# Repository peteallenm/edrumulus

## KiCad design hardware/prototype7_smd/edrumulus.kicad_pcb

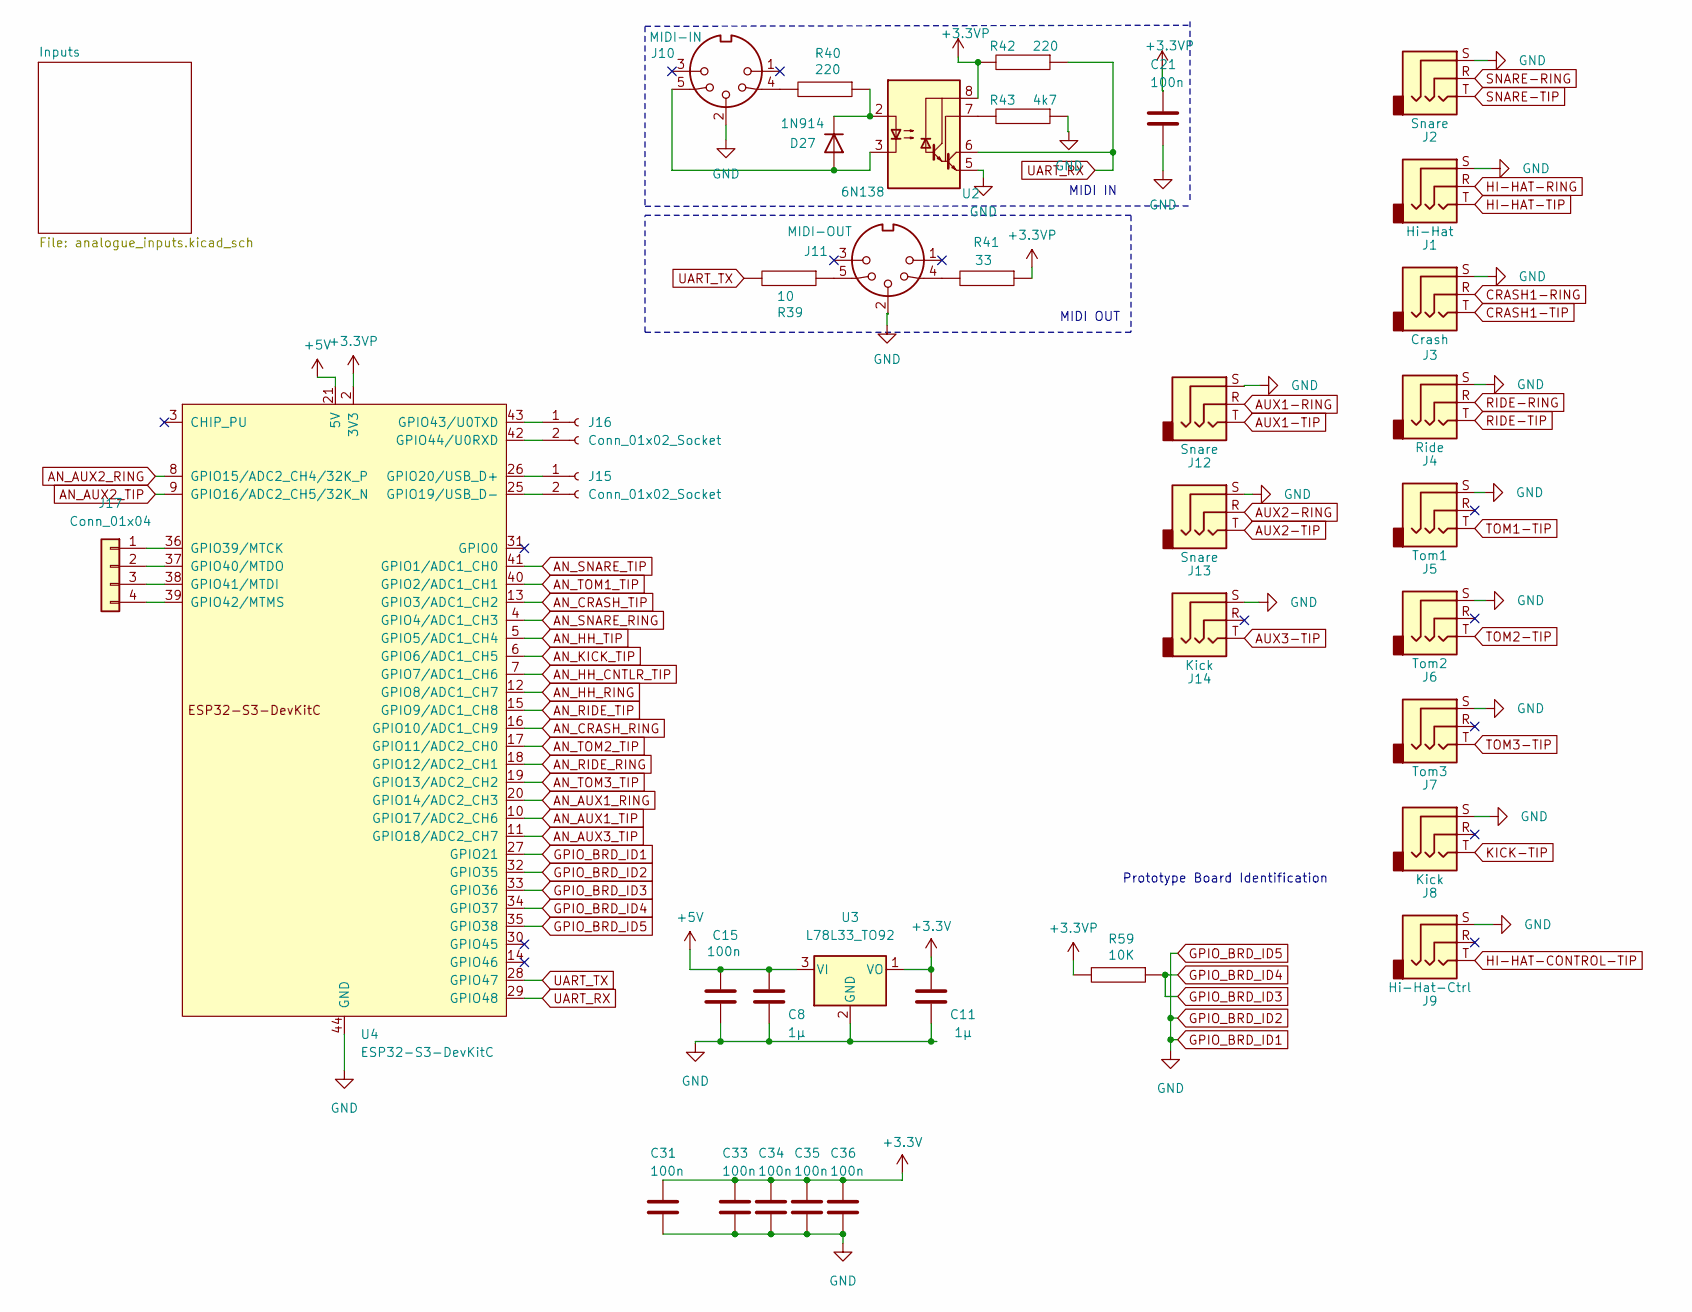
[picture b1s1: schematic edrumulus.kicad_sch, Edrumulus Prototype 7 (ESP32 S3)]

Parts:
C8, C11: 1µ; C_1206_3216Metric
C15, C21, C31, C33, C34, C35, C36: 100n; C_1206_3216Metric
D27: 1N914; D_DO-35_SOD27_P7.62mm_Horizontal
J1: Hi-Hat; Jack_6.35mm_Neutrik_NMJ6HCD2_Horizontal
J2, J12, J13: Snare; Jack_6.35mm_Neutrik_NMJ6HCD2_Horizontal
J3: Crash; Jack_6.35mm_Neutrik_NMJ6HCD2_Horizontal
J4: Ride; Jack_6.35mm_Neutrik_NMJ6HCD2_Horizontal
J5: Tom1; Jack_6.35mm_Neutrik_NMJ6HCD2_Horizontal
J6: Tom2; Jack_6.35mm_Neutrik_NMJ6HCD2_Horizontal
J7: Tom3; Jack_6.35mm_Neutrik_NMJ6HCD2_Horizontal
J8, J14: Kick; Jack_6.35mm_Neutrik_NMJ6HCD2_Horizontal
J9: Hi-Hat-Ctrl; Jack_6.35mm_Neutrik_NMJ6HCD2_Horizontal
J10: MIDI-IN; DIN-5
J11: MIDI-OUT; DIN-5
J15, J16: Conn_01x02_Socket; PinHeader_1x02_P2.54mm_Vertical
J17: Conn_01x04; PinHeader_1x04_P2.54mm_Vertical
R39: 10; R_1206_3216Metric
R40, R42: 220; R_1206_3216Metric
R41: 33; R_1206_3216Metric
R43: 4k7; R_1206_3216Metric
R59: 10K; R_1206_3216Metric
U2: 6N138; DIP-8_W7.62mm_Socket
U3: L78L33_TO92; TO-92_Inline
U4: ESP32-S3-DevKitC

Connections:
+3.3V: C11.1, C31.1, C33.1, C34.1, C35.1, C36.1, U3.1 (VO); also elsewhere on the board
+3.3VP: C21.1, R41.1, R42.2, R59.2, U2.8 (VCC), U4.1 (3V3), U4.2 (3V3)
+5V: C8.1, C15.1, U3.3 (VI), U4.21 (5V)
AN_AUX1_RING: U4.20 (GPIO14/ADC2_CH3); also elsewhere on the board
AN_AUX1_TIP: U4.10 (GPIO17/ADC2_CH6); also elsewhere on the board
AN_AUX2_RING: U4.8 (GPIO15/ADC2_CH4/32K_P); also elsewhere on the board
AN_AUX2_TIP: U4.9 (GPIO16/ADC2_CH5/32K_N); also elsewhere on the board
AN_AUX3_TIP: U4.11 (GPIO18/ADC2_CH7); also elsewhere on the board
AN_CRASH_RING: U4.16 (GPIO10/ADC1_CH9); also elsewhere on the board
AN_CRASH_TIP: U4.13 (GPIO3/ADC1_CH2); also elsewhere on the board
AN_HH_CNTLR_TIP: U4.7 (GPIO7/ADC1_CH6); also elsewhere on the board
AN_HH_RING: U4.12 (GPIO8/ADC1_CH7); also elsewhere on the board
AN_HH_TIP: U4.5 (GPIO5/ADC1_CH4); also elsewhere on the board
AN_KICK_TIP: U4.6 (GPIO6/ADC1_CH5); also elsewhere on the board
AN_RIDE_RING: U4.18 (GPIO12/ADC2_CH1); also elsewhere on the board
AN_RIDE_TIP: U4.15 (GPIO9/ADC1_CH8); also elsewhere on the board
AN_SNARE_RING: U4.4 (GPIO4/ADC1_CH3); also elsewhere on the board
AN_SNARE_TIP: U4.41 (GPIO1/ADC1_CH0); also elsewhere on the board
AN_TOM1_TIP: U4.40 (GPIO2/ADC1_CH1); also elsewhere on the board
AN_TOM2_TIP: U4.17 (GPIO11/ADC2_CH0); also elsewhere on the board
AN_TOM3_TIP: U4.19 (GPIO13/ADC2_CH2); also elsewhere on the board
AUX1-RING: J12.R; also elsewhere on the board
AUX1-TIP: J12.T; also elsewhere on the board
AUX2-RING: J13.R; also elsewhere on the board
AUX2-TIP: J13.T; also elsewhere on the board
AUX3-TIP: J14.T; also elsewhere on the board
CRASH1-RING: J3.R; also elsewhere on the board
CRASH1-TIP: J3.T; also elsewhere on the board
GPIO_BRD_ID1: C8.2, C11.2, C15.2, C21.2, C31.2, C33.2, C34.2, C35.2, C36.2, J1.S, J2.S, J3.S, J4.S, J5.S, J6.S, J7.S, J8.S, J9.S, J10.2, J11.2, J12.S, J13.S, J14.S, R43.1, U2.5 (GND), U3.2 (GND), U4.22 (GND), U4.23 (GND), U4.24 (GND), U4.27 (GPIO21), U4.32 (GPIO35), U4.35 (GPIO38), U4.44 (GND); also elsewhere on the board
GPIO_BRD_ID3: R59.1, U4.33 (GPIO36), U4.34 (GPIO37)
HI-HAT-CONTROL-TIP: J9.T; also elsewhere on the board
HI-HAT-RING: J1.R; also elsewhere on the board
HI-HAT-TIP: J1.T; also elsewhere on the board
KICK-TIP: J8.T; also elsewhere on the board
unnamed: D27.2 (A), J10.5, U2.3 (C2)
unnamed: D27.1 (K), R40.1, U2.2 (C1)
unnamed: J10.4, R40.2
unnamed: J11.4, R41.2
unnamed: J11.5, R39.1
unnamed: J15.1, U4.26 (GPIO20/USB_D+)
unnamed: J15.2, U4.25 (GPIO19/USB_D-)
unnamed: J16.1, U4.43 (GPIO43/U0TXD)
unnamed: J16.2, U4.42 (GPIO44/U0RXD)
unnamed: J17.1, U4.36 (GPIO39/MTCK)
unnamed: J17.2, U4.37 (GPIO40/MTDO)
unnamed: J17.3, U4.38 (GPIO41/MTDI)
unnamed: J17.4, U4.39 (GPIO42/MTMS)
unnamed: R43.2, U2.7 (VO1)
RIDE-RING: J4.R; also elsewhere on the board
RIDE-TIP: J4.T; also elsewhere on the board
SNARE-RING: J2.R; also elsewhere on the board
SNARE-TIP: J2.T; also elsewhere on the board
TOM1-TIP: J5.T; also elsewhere on the board
TOM2-TIP: J6.T; also elsewhere on the board
TOM3-TIP: J7.T; also elsewhere on the board
UART_RX: R42.1, U2.6 (VO2), U4.29 (GPIO48)
UART_TX: R39.2, U4.28 (GPIO47)

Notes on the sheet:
MIDI OUT
Prototype Board Identification
MIDI IN

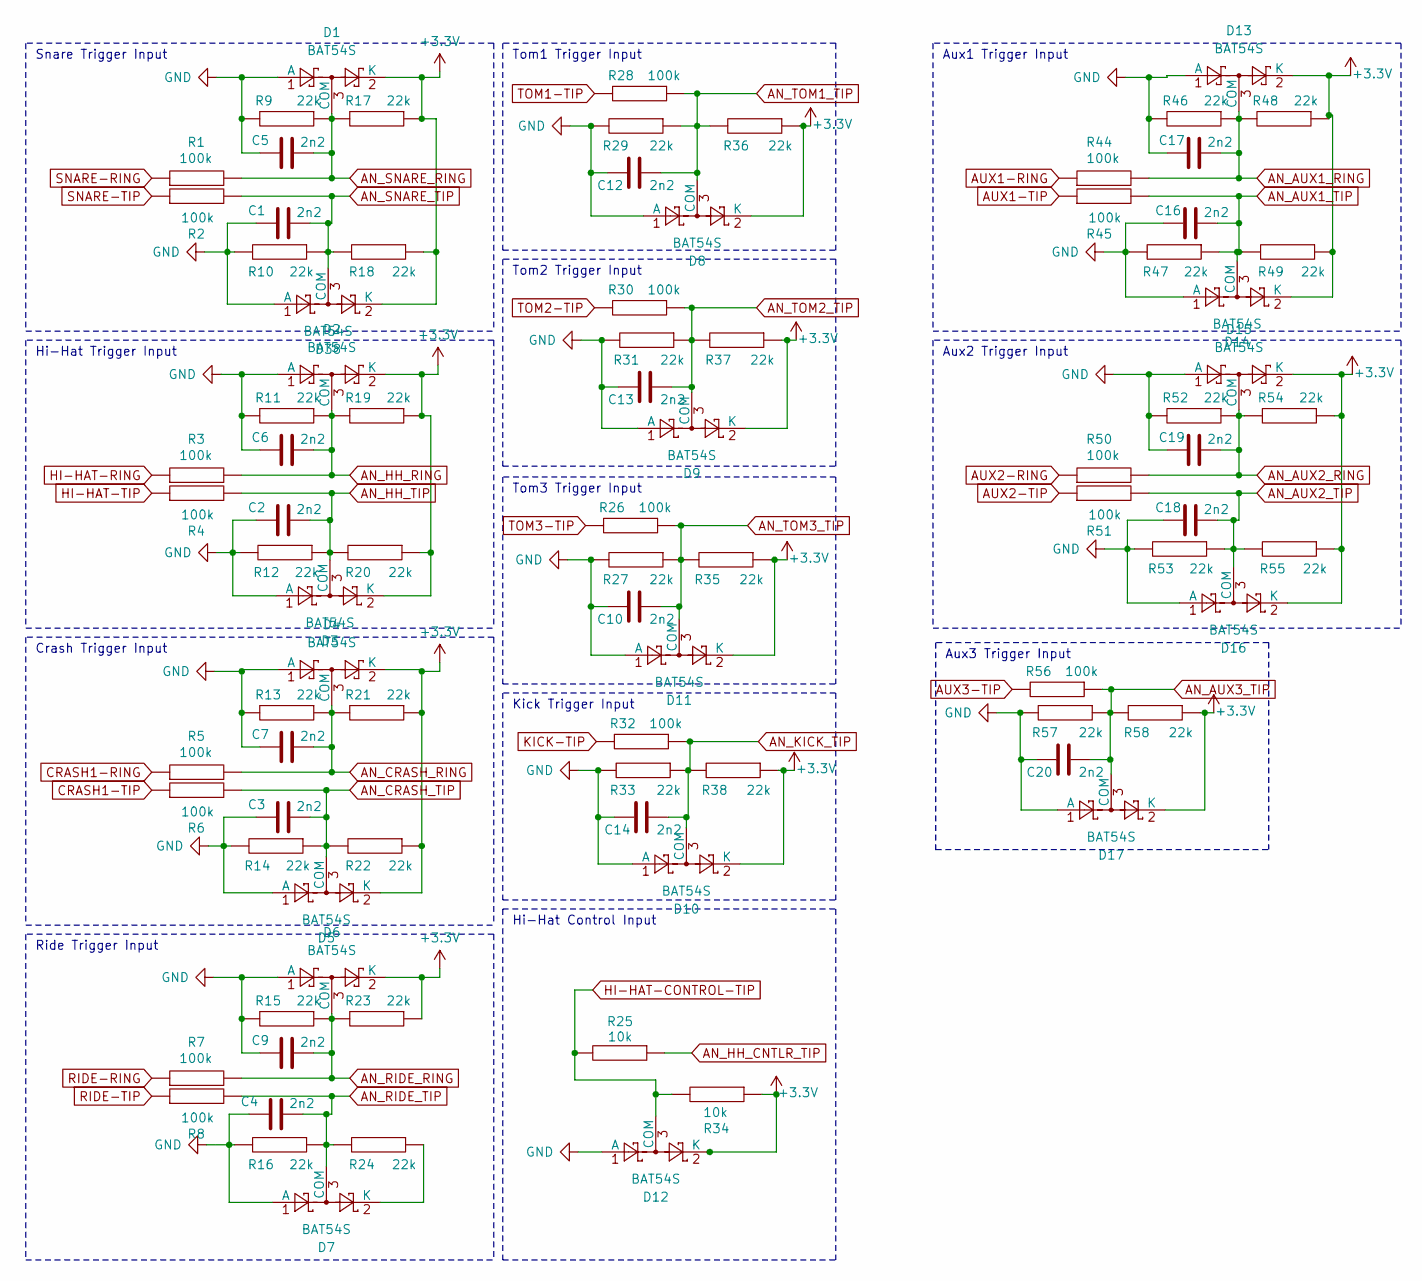
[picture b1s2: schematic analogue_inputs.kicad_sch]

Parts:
C1, C2, C3, C4, C5, C6, C7, C9, C10, C12, C13, C14, C16, C17, C18, C19, C20: 2n2; C_1206_3216Metric
D1, D2, D3, D4, D5, D6, D7, D8, D9, D10, D11, D12, D13, D14, D15, D16, D17, D38: BAT54S; SOT-23
R1, R2, R3, R4, R5, R6, R7, R8, R26, R28, R30, R32, R44, R45, R50, R51, R56: 100k; R_1206_3216Metric
R9, R10, R11, R12, R13, R14, R15, R16, R17, R18, R19, R20, R21, R22, R23, R24, R27, R29, R31, R33, R35, R36, R37, R38, R46, R47, R48, R49, R52, R53, R54, R55, R57, R58: 22k; R_1206_3216Metric
R25, R34: 10k; R_1206_3216Metric

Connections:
+3.3V: D1.2 (K), D2.2 (K), D3.2 (K), D4.2 (K), D5.2 (K), D6.2 (K), D8.2 (K), D9.2 (K), D10.2 (K), D11.2 (K), D12.2 (K), D13.2 (K), D14.2 (K), D15.2 (K), D16.2 (K), D17.2 (K), D38.2 (K), R17.1, R18.1, R19.1, R20.1, R21.1, R22.1, R23.1, R34.1, R35.1, R36.1, R37.1, R38.1, R48.1, R49.1, R54.1, R55.1, R58.1; also elsewhere on the board
AN_AUX1_RING: C17.1, D13.3 (COM), R44.2, R46.1, R48.2; also elsewhere on the board
AN_AUX1_TIP: C16.1, D14.3 (COM), R45.2, R47.1, R49.2; also elsewhere on the board
AN_AUX2_RING: C19.1, D15.3 (COM), R50.2, R52.1, R54.2; also elsewhere on the board
AN_AUX2_TIP: C18.1, D16.3 (COM), R51.2, R53.1, R55.2; also elsewhere on the board
AN_AUX3_TIP: R56.1; also elsewhere on the board
AN_CRASH_RING: C7.1, D4.3 (COM), R5.2, R13.1, R21.2; also elsewhere on the board
AN_CRASH_TIP: C3.1, D5.3 (COM), R6.2, R14.1, R22.2; also elsewhere on the board
AN_HH_CNTLR_TIP: R25.1; also elsewhere on the board
AN_HH_RING: C6.1, D2.3 (COM), R3.2, R11.1, R19.2; also elsewhere on the board
AN_HH_TIP: C2.1, D3.3 (COM), R4.2, R12.1, R20.2; also elsewhere on the board
AN_KICK_TIP: R32.1; also elsewhere on the board
AN_RIDE_RING: C9.1, D6.3 (COM), R7.2, R15.1, R23.2; also elsewhere on the board
AN_RIDE_TIP: C4.1, D7.3 (COM), R8.2, R16.1, R24.2; also elsewhere on the board
AN_SNARE_RING: C5.1, D1.3 (COM), R1.2, R9.1, R17.2; also elsewhere on the board
AN_SNARE_TIP: C1.1, D38.3 (COM), R2.2, R10.1, R18.2; also elsewhere on the board
AN_TOM1_TIP: C12.1, D8.3 (COM), R28.1, R29.1, R36.2; also elsewhere on the board
AN_TOM2_TIP: C13.1, D9.3 (COM), R30.1, R31.1, R37.2; also elsewhere on the board
AN_TOM3_TIP: C10.1, D11.3 (COM), R26.1, R27.1, R35.2; also elsewhere on the board
AUX1-RING: R44.1; also elsewhere on the board
AUX1-TIP: R45.1; also elsewhere on the board
AUX2-RING: R50.1; also elsewhere on the board
AUX2-TIP: R51.1; also elsewhere on the board
AUX3-TIP: R56.2; also elsewhere on the board
CRASH1-RING: R5.1; also elsewhere on the board
CRASH1-TIP: R6.1; also elsewhere on the board
GPIO_BRD_ID1: C1.2, C2.2, C3.2, C5.2, C6.2, C7.2, C9.2, C10.2, C12.2, C13.2, C14.2, C16.2, C17.2, C18.2, C19.2, C20.2, D1.1 (A), D2.1 (A), D3.1 (A), D4.1 (A), D5.1 (A), D6.1 (A), D8.1 (A), D9.1 (A), D10.1 (A), D11.1 (A), D12.1 (A), D13.1 (A), D14.1 (A), D15.1 (A), D16.1 (A), D17.1 (A), D38.1 (A), R9.2, R10.2, R11.2, R12.2, R13.2, R14.2, R15.2, R27.2, R29.2, R31.2, R33.2, R46.2, R47.2, R52.2, R53.2, R57.2; also elsewhere on the board
HI-HAT-CONTROL-TIP: D12.3 (COM), R25.2, R34.2; also elsewhere on the board
HI-HAT-RING: R3.1; also elsewhere on the board
HI-HAT-TIP: R4.1; also elsewhere on the board
KICK-TIP: R32.2; also elsewhere on the board
unnamed: C4.2, D7.1 (A), R16.2
unnamed: D7.2 (K), R24.1
unnamed: C14.1, D10.3 (COM), R33.1, R38.2
unnamed: C20.1, D17.3 (COM), R57.1, R58.2
RIDE-RING: R7.1; also elsewhere on the board
RIDE-TIP: R8.1; also elsewhere on the board
SNARE-RING: R1.1; also elsewhere on the board
SNARE-TIP: R2.1; also elsewhere on the board
TOM1-TIP: R28.2; also elsewhere on the board
TOM2-TIP: R30.2; also elsewhere on the board
TOM3-TIP: R26.2; also elsewhere on the board

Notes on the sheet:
Tom1 Trigger Input
Aux3 Trigger Input
Tom3 Trigger Input
Hi-Hat Trigger Input
Aux1 Trigger Input
Ride Trigger Input
Kick Trigger Input
Snare Trigger Input
Tom2 Trigger Input
Crash Trigger Input
Aux2 Trigger Input
Hi-Hat Control Input

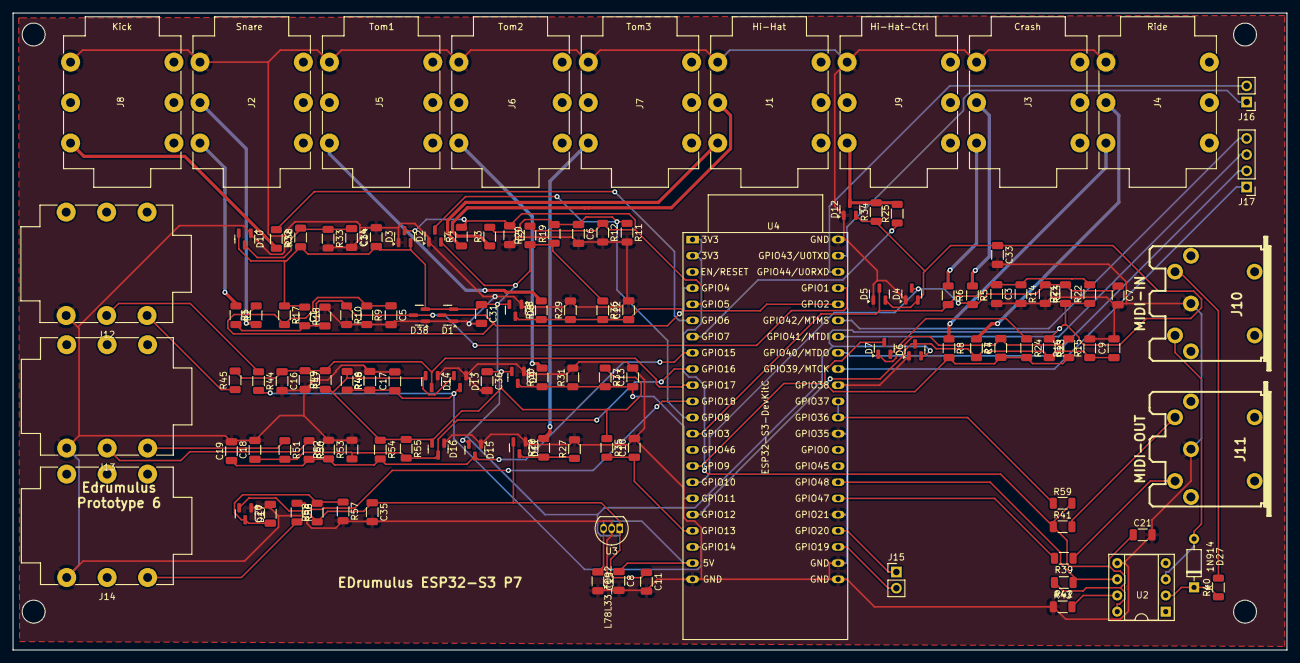
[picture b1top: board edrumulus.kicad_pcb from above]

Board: 2 copper layers, 200.0 x 100.0 mm, 124 parts (0 on the bottom side), 61 nets.

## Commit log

2024-10-20 Add first version of the SMD
2024-10-21 Fix routing
2024-10-21 Update gerbers
2024-10-21 Remove backups
2024-10-23 rename to prototype_petea_smd
2024-10-23 rename prototype
2024-10-23 Add some performance stats
2024-10-26 Move to tasks for Drums and Midi
2024-10-29 Add webpage debug and visualisation
2024-10-30 Fix the debug plot
